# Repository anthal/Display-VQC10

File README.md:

# VQC10
DDR (WF) Punkt-Matrix-LED-Display VQC10 (Leiterplatte und Code)

Version 1

Version 2

## Leiterplatte Version 2
### Platine
* Farbe der Platine V.1 auf den Bildern: rot
* Farbe der Platine V.2 auf den Bildern: schwarz
* KiCAD 9 Projekt
* Die Platinen sind nebeneinander anreihbar und es können bis zu 4 Stück kaskadiert werden.
* Ab der 2. Platine geht es mit Flachbandkabel zur nächsten Platine. 
* Jede Platine wird über eine eigene Leitung (SD4-SD7) aktiviert. Die Auswahl erfolgt über die 4 Jumper.

### Halbleiterbauelemente
* 4 x VQC 10 (4-Digit-Punkt-Matrix-LED-Displays) 
* 3 x 74LS138 (1-aus-8 Dekoder für Zeilen und 1-aus-16 Dekoder für Digits)
* 1 x 74LS123 (Schutzschaltung)
* 7 x BD140 (Zeilentreiber)

### Anschlüsse Leiterplatte Version 1
**An 20 pol. Steckerleiste:**
* ZD0 - ZD2 (3): Zeilendecoder (U1, 74HCT138)
* SD0 - SD3 (4): Stellendecoder (U2, U3, 2x 74HCT138)
* SD4 - SD7 (4): Selektierung der Stellendecoder über Jumper (Low-Aktiv)
* D1-D5 (5): Daten (Zeilen)

**Belegung der Anschlüsse:**
| Pin | Belegung | Raspberry Pi Pico | LC80ex | Pin LC80-Userport |
|-----|----------|-------------------|--------|-------------------|
| 1   | +5 V     | +5 V              | +5 V   | 26                |
| 2   | +5 V     | +5 V              | +5 V   | 25                |
| 3   | SD0      | GP20              | PB0    | 16                |
| 4   | ZD0      | GP15              | PA0    | 21                |
| 5   | SD1      | GP19              | PB1    | 18                |
| 6   | ZD1      | GP14              | PA1    | 19                |
| 7   | SD2      | GP18              | PB2    | 20                |
| 8   | ZD2      | GP12              | PA2    | 17                |
| 9   | SD3      | GP17              | PB3    | 22                |
| 10  | D1       | GP28              | PA3    | 7                 |
| 11  | SD4      | GP16              | (Masse)| -                 |
| 12  | D2       | GP27              | PA4    | 9                 |
| 13  | SD5      | GP10              | (Masse)| -                 |
| 14  | D3       | GP26              | PA5    | 11                |
| 15  | SD6      | GP9               | (Masse)| -                 |
| 16  | D4       | GP22              | PA6    | 13                |
| 17  | SD7      | GP8               | (Masse)| -                 |
| 18  | D5       | GP21              | PA7    | 15                |
| 19  | Masse    | Masse             | Masse  | 1                 |
| 20  | Masse    | Masse             | Masse  | 2                 |

### Selektion der 4 Leiterplatten
SD4-7 müssen zur Selektierung Low und der jeweilige Jumper geschlossen sein:
| Leiterplatte | Jumper | Pin (J1/J2) | Belegung | Port-Pin (Raspberry Pi Pico) |
|---|-----|----|-----|------|
| 1 | JP1 | 11 | SD4 | GP16 |
| 2 | JP2 | 13 | SD5 | GP10 |
| 3 | JP3 | 15 | SD6 | GP9 |
| 4 | JP4 | 17 | SD7 | GP8 |

**Leiterplatte 1:** 
* Jumper JP1 geschlossen
* Jumper JP2 geöffnet
* Jumper JP3 geöffnet
* Jumper JP4 geöffnet

**Leiterplatte 2:**
* Jumper JP1 geöffnet
* Jumper JP2 geschlossen
* Jumper JP3 geöffnet
* Jumper JP4 geöffnet

**Leiterplatte 3:**
* Jumper JP1 geöffnet
* Jumper JP2 geöffnet
* Jumper JP3 geschlossen
* Jumper JP4 geöffnet

**Leiterplatte 4:**
* Jumper JP1 geöffnet
* Jumper JP2 geöffnet
* Jumper JP3 geöffnet
* Jumper JP4 geschlossen

## Literatur
* Datenblatt
* Schaltungen aus der rfe

## Simulation
* Simulation von 1x VQC10 mit Z80 unter SimulIDE
* https://simulide.com/

## Software
### Arduino Code
* Für den Raspberry Pi Pico
* auf Basis von https://github.com/versioduo/VQC10
* Vor Compilierung Example Datei und Files aus scr Verzeichnis in ein gemeinsames Verzeichnis verschieben

### Micropython Code
* Für den Raspberry Pi Pico

### Z80-Assembler
#### aZ80/RC2016-Computer

4x VQC10 am aZ80 Computer

Benutzte Entwicklungssoftware:
* "Small Computer-Monitor"
* https://smallcomputercentral.com/small-computer-monitor/

#### LC80ex

Test mit dem Nachbau des DDR-Platinen Computers LC80 

#### Z1013
ToDo

## Gehäuse

Grundplatte für IKEA Bilderrahmmen "VÄSTANHED 20x25 cm" mit Leiterplatten der Version 1
* STL Datei für 3D-Druck: "Gehäuse/2xVQC10_Grundplatte1.stl"

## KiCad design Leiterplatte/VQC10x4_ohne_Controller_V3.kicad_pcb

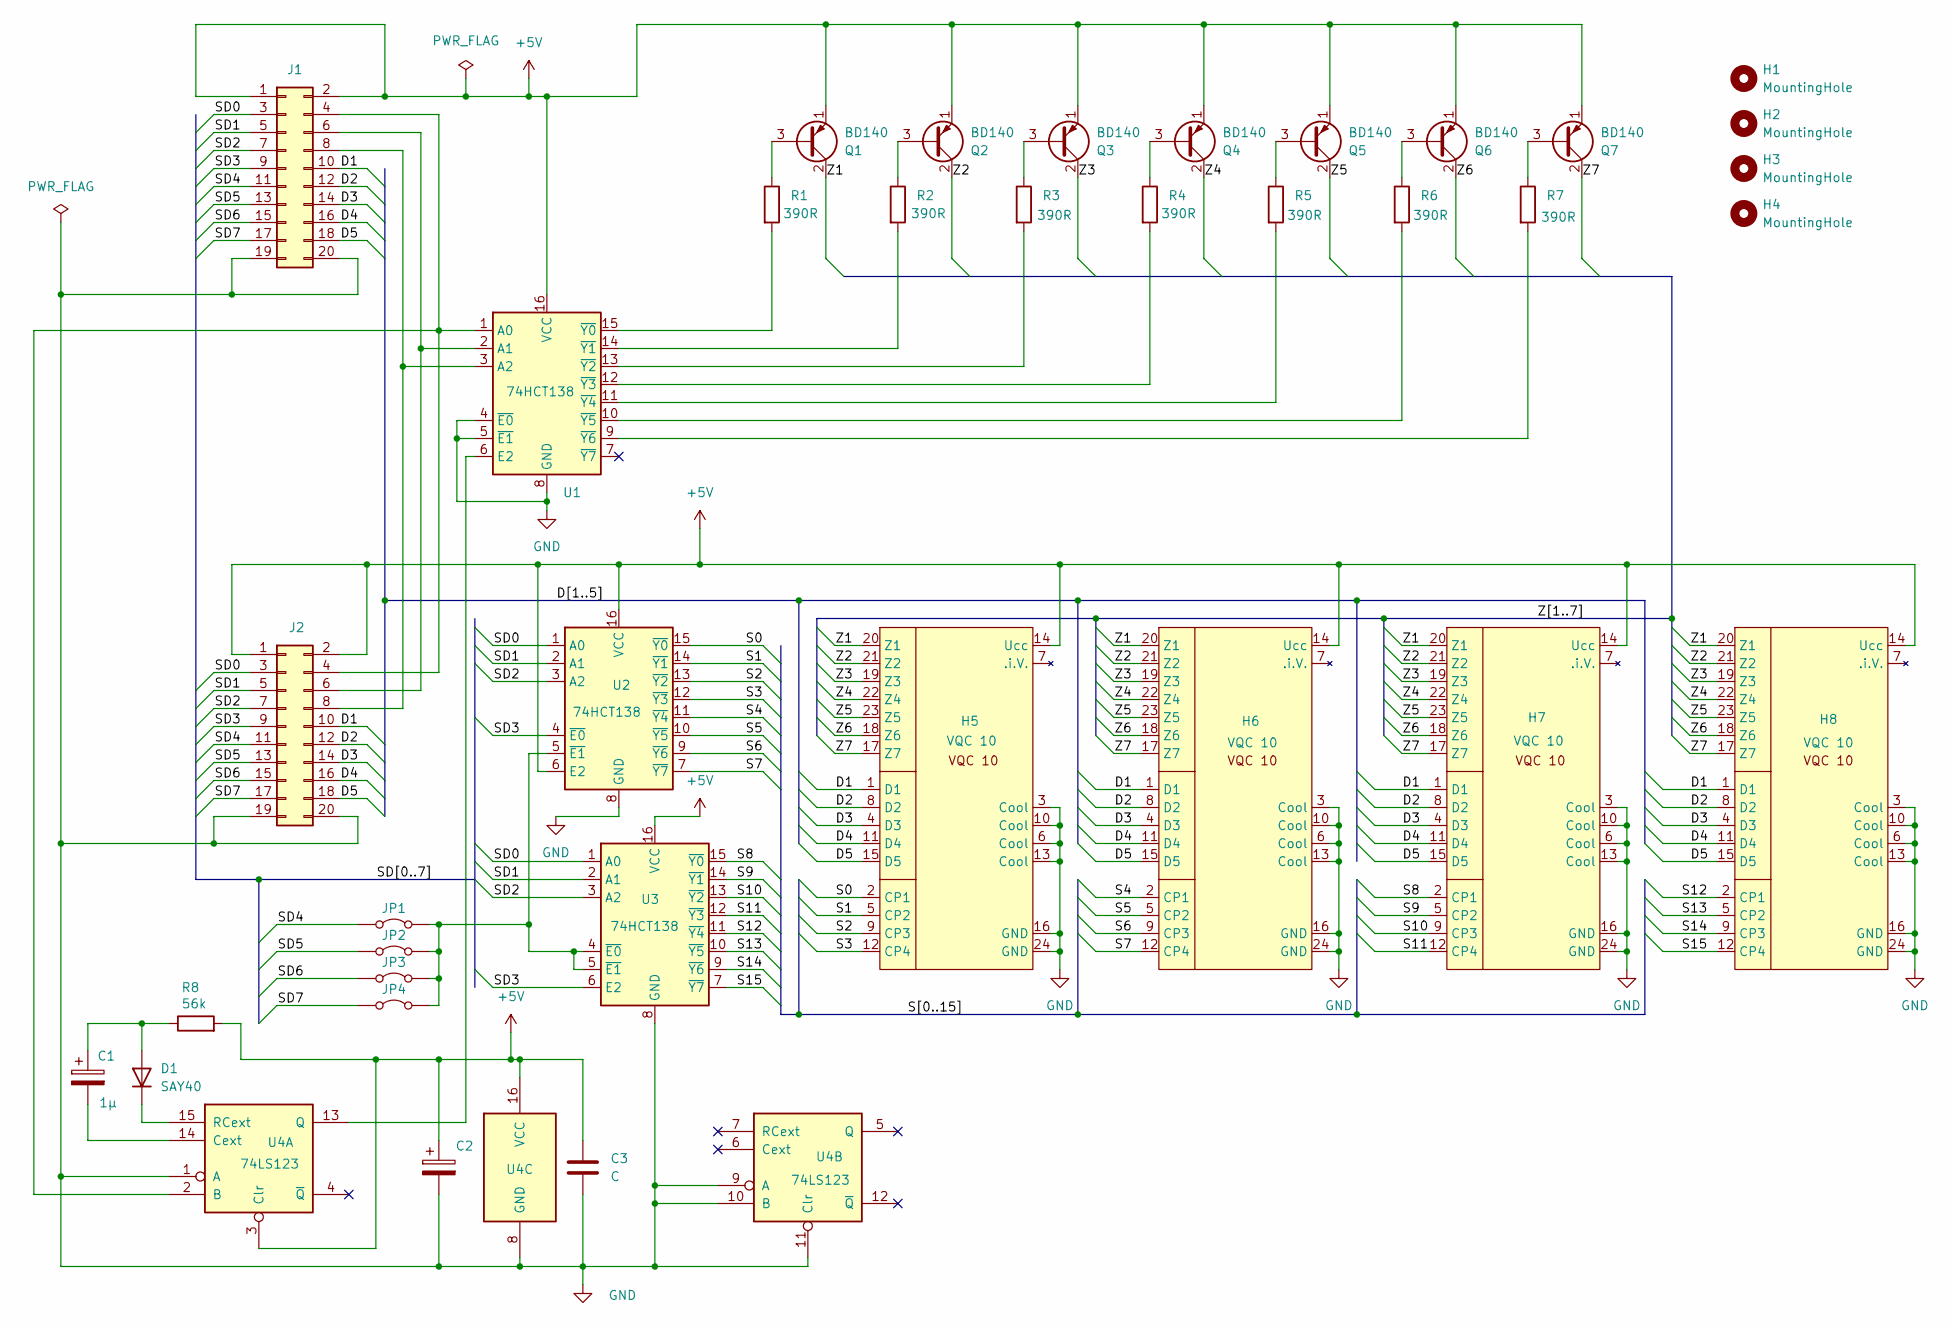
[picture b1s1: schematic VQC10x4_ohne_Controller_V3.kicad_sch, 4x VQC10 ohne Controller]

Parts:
C1: 1µ; CP_Radial_D5.0mm_P2.50mm
C2: C_Polarized; CP_Radial_D6.3mm_P2.50mm
C3: C; C_Disc_D5.0mm_W2.5mm_P2.50mm
D1: SAY40; D_A-405_P7.62mm_Horizontal
H1, H2, H3, H4: MountingHole; MountingHole_3.2mm_M3
H5, H6, H7, H8: VQC 10; VQC10
J1, J2: Conn_02x10_Odd_Even; IDC-Header_2x10_P2.54mm_Horizontal
JP1, JP2, JP3, JP4: Jumper_2_Bridged; TestPoint_2Pads_Pitch2.54mm_Drill0.8mm
Q1, Q2, Q3, Q4, Q5, Q6, Q7: BD140; TO-126-3_Vertical
R1, R2, R3, R4, R5, R6, R7: 390R; R_Axial_DIN0204_L3.6mm_D1.6mm_P5.08mm_Horizontal
R8: 56k; R_Axial_DIN0207_L6.3mm_D2.5mm_P7.62mm_Horizontal
U1, U2, U3: 74HCT138; DIP-16_W7.62mm_LongPads
U4: 74LS123; DIP-16_W7.62mm_LongPads

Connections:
+5V: C2.1, C3.1, H5.14 (Ucc), H6.14 (Ucc), H7.14 (Ucc), H8.14 (Ucc), J1.1, J1.2, J2.1, J2.2, Q1.1 (E), Q2.1 (E), Q3.1 (E), Q4.1 (E), Q5.1 (E), Q6.1 (E), Q7.1 (E), R8.2, U1.16 (VCC), U2.6 (E2), U2.16 (VCC), U3.16 (VCC), U4.3 (Clr), U4.16 (VCC)
/D1: H5.1 (D1), H6.1 (D1), H7.1 (D1), H8.1 (D1), J1.10, J2.10
/D2: H5.8 (D2), H6.8 (D2), H7.8 (D2), H8.8 (D2), J1.12, J2.12
/D3: H5.4 (D3), H6.4 (D3), H7.4 (D3), H8.4 (D3), J1.14, J2.14
/D4: H5.11 (D4), H6.11 (D4), H7.11 (D4), H8.11 (D4), J1.16, J2.16
/D5: H5.15 (D5), H6.15 (D5), H7.15 (D5), H8.15 (D5), J1.18, J2.18
/S0: H5.2 (CP1), U2.15 (~Y0)
/S1: H5.5 (CP2), U2.14 (~Y1)
/S2: H5.9 (CP3), U2.13 (~Y2)
/S3: H5.12 (CP4), U2.12 (~Y3)
/S4: H6.2 (CP1), U2.11 (~Y4)
/S5: H6.5 (CP2), U2.10 (~Y5)
/S6: H6.9 (CP3), U2.9 (~Y6)
/S7: H6.12 (CP4), U2.7 (~Y7)
/S8: H7.2 (CP1), U3.15 (~Y0)
/S9: H7.5 (CP2), U3.14 (~Y1)
/S10: H7.9 (CP3), U3.13 (~Y2)
/S11: H7.12 (CP4), U3.12 (~Y3)
/S12: H8.2 (CP1), U3.11 (~Y4)
/S13: H8.5 (CP2), U3.10 (~Y5)
/S14: H8.9 (CP3), U3.9 (~Y6)
/S15: H8.12 (CP4), U3.7 (~Y7)
/SD0: J1.3, J2.3, U2.1 (A0), U3.1 (A0)
/SD1: J1.5, J2.5, U2.2 (A1), U3.2 (A1)
/SD2: J1.7, J2.7, U2.3 (A2), U3.3 (A2)
/SD3: J1.9, J2.9, U2.4 (~E0), U3.6 (E2)
/SD4: J1.11, J2.11, JP1.1 (A)
/SD5: J1.13, J2.13, JP2.1 (A)
/SD6: J1.15, J2.15, JP3.1 (A)
/SD7: J1.17, J2.17, JP4.1 (A)
/Z1: H5.20 (Z1), H6.20 (Z1), H7.20 (Z1), H8.20 (Z1), Q1.2 (C)
/Z2: H5.21 (Z2), H6.21 (Z2), H7.21 (Z2), H8.21 (Z2), Q2.2 (C)
/Z3: H5.19 (Z3), H6.19 (Z3), H7.19 (Z3), H8.19 (Z3), Q3.2 (C)
/Z4: H5.22 (Z4), H6.22 (Z4), H7.22 (Z4), H8.22 (Z4), Q4.2 (C)
/Z5: H5.23 (Z5), H6.23 (Z5), H7.23 (Z5), H8.23 (Z5), Q5.2 (C)
/Z6: H5.18 (Z6), H6.18 (Z6), H7.18 (Z6), H8.18 (Z6), Q6.2 (C)
/Z7: H5.17 (Z7), H6.17 (Z7), H7.17 (Z7), H8.17 (Z7), Q7.2 (C)
GND: C2.2, C3.2, H5.3 (Cool), H5.6 (Cool), H5.10 (Cool), H5.13 (Cool), H5.16 (GND), H5.24 (GND), H6.3 (Cool), H6.6 (Cool), H6.10 (Cool), H6.13 (Cool), H6.16 (GND), H6.24 (GND), H7.3 (Cool), H7.6 (Cool), H7.10 (Cool), H7.13 (Cool), H7.16 (GND), H7.24 (GND), H8.3 (Cool), H8.6 (Cool), H8.10 (Cool), H8.13 (Cool), H8.16 (GND), H8.24 (GND), J1.19, J1.20, J2.19, J2.20, U1.4 (~E0), U1.5 (~E1), U1.8 (GND), U2.8 (GND), U3.8 (GND), U4.1 (A), U4.8 (GND), U4.9 (A), U4.10 (B), U4.11 (Clr)
unnamed: C1.1, D1.2 (A), R8.1
unnamed: D1.1 (K), U4.15 (RCext)
unnamed: J1.4, J2.4, U1.1 (A0), U4.2 (B)
unnamed: J1.6, J2.6, U1.2 (A1)
unnamed: J1.8, J2.8, U1.3 (A2)
unnamed: JP1.2 (B), JP2.2 (B), JP3.2 (B), JP4.2 (B), U2.5 (~E1), U3.4 (~E0), U3.5 (~E1)
unnamed: Q1.3 (B), R1.1
unnamed: Q2.3 (B), R2.1
unnamed: Q3.3 (B), R3.1
unnamed: Q4.3 (B), R4.1
unnamed: Q5.3 (B), R5.1
unnamed: Q6.3 (B), R6.1
unnamed: Q7.3 (B), R7.1
unnamed: U1.6 (E2), U4.13 (Q)
unnamed: R1.2, U1.15 (~Y0)
unnamed: R2.2, U1.14 (~Y1)
unnamed: R3.2, U1.13 (~Y2)
unnamed: R4.2, U1.12 (~Y3)
unnamed: R5.2, U1.11 (~Y4)
unnamed: R6.2, U1.10 (~Y5)
unnamed: R7.2, U1.9 (~Y6)
unnamed: C1.2, U4.14 (Cext)

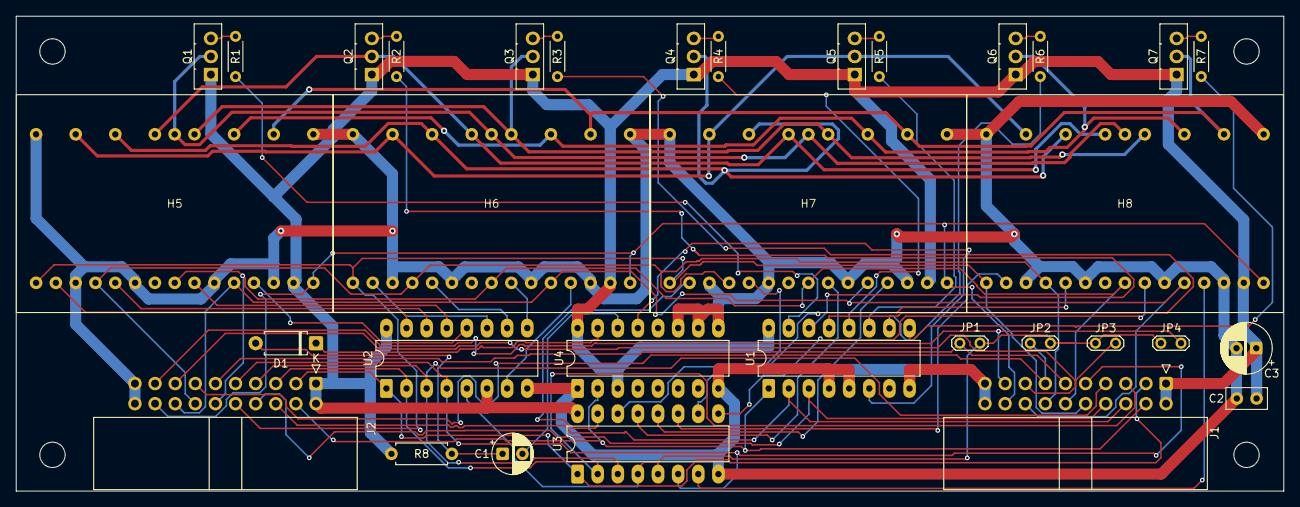
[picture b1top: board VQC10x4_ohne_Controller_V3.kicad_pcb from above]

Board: 2 copper layers, 160.0 x 59.9 mm, 37 parts (0 on the bottom side), 60 nets.

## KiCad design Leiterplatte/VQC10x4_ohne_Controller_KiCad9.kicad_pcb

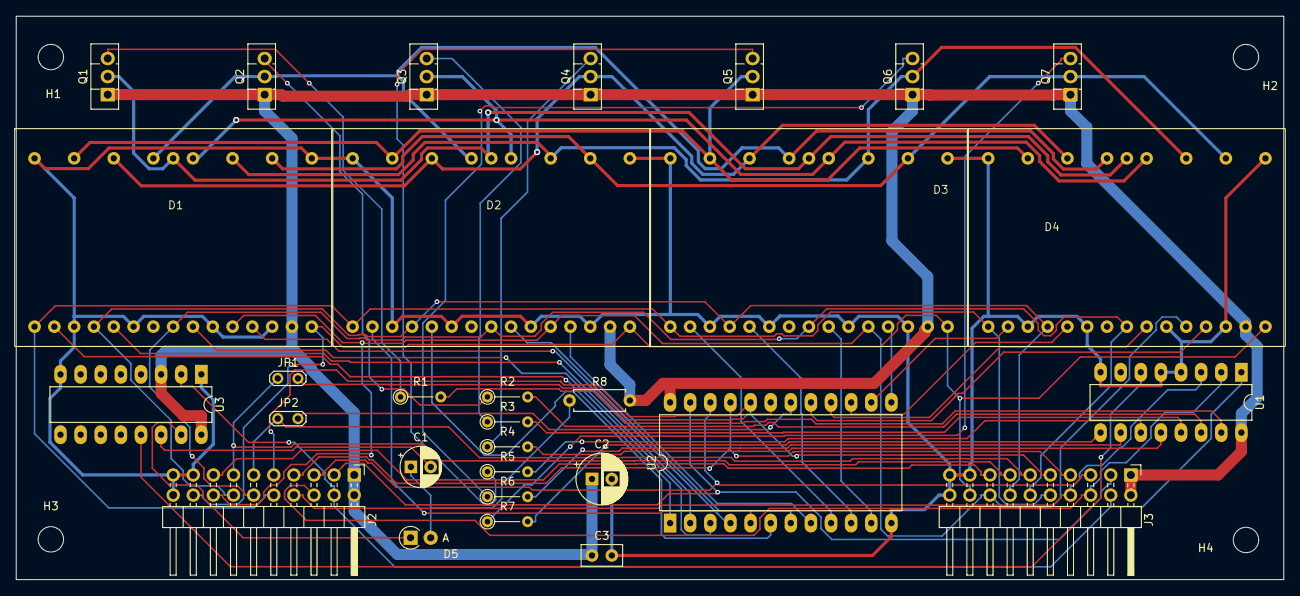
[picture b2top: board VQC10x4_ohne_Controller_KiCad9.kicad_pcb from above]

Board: 2 copper layers, 160.0 x 71.1 mm, 34 parts (0 on the bottom side), 60 nets.

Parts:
C1: 1µ; CP_Radial_D5.0mm_P2.50mm
C2: C_Polarized; CP_Radial_D6.3mm_P2.50mm
C3: C; C_Disc_D5.0mm_W2.5mm_P2.50mm
D1, D2, D3, D4: VQC 10; VQC10
D5: SAY40; D_A-405_P2.54mm_Vertical_AnodeUp
H1, H2, H3, H4: MountingHole; MountingHole_3.2mm_M3
J2, J3: Conn_02x10_Odd_Even; PinHeader_2x10_P2.54mm_Horizontal
JP1, JP2: Jumper_2_Bridged; TestPoint_2Pads_Pitch2.54mm_Drill0.8mm
Q1, Q2, Q3, Q4, Q5, Q6, Q7: BD140; TO-126-3_Vertical
R1, R2, R3, R4, R5, R6, R7: R; R_Axial_DIN0204_L3.6mm_D1.6mm_P5.08mm_Vertical
R8: 56k; R_Axial_DIN0207_L6.3mm_D2.5mm_P7.62mm_Horizontal
U1: 74HCT138; DIP-16_W7.62mm_LongPads
U2: 74LS154; DIP-24_W15.24mm_LongPads
U3: 74LS123; DIP-16_W7.62mm_LongPads

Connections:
+5V: C2.1, C3.1, D1.14 (Ucc), D2.14 (Ucc), D3.14 (Ucc), D4.14 (Ucc), J2.1, J2.2, J3.1, J3.2, Q1.1 (E), Q2.1 (E), Q3.1 (E), Q4.1 (E), Q5.1 (E), Q6.1 (E), Q7.1 (E), R8.2, U1.16 (VCC), U2.24 (VCC), U3.3 (Clr), U3.16 (VCC)
/D1: D1.1 (D1), D2.1 (D1), D3.1 (D1), D4.1 (D1), J2.10, J3.10
/D2: D1.8 (D2), D2.8 (D2), D3.8 (D2), D4.8 (D2), J2.12, J3.12
/D3: D1.4 (D3), D2.4 (D3), D3.4 (D3), D4.4 (D3), J2.14, J3.14
/D4: D1.11 (D4), D2.11 (D4), D3.11 (D4), D4.11 (D4), J2.16, J3.16
/D5: D1.15 (D5), D2.15 (D5), D3.15 (D5), D4.15 (D5), J2.18, J3.18
/S0: D1.2 (CP1), U2.1 (S0)
/S1: D1.5 (CP2), U2.2 (S1)
/S2: D1.9 (CP3), U2.3 (S2)
/S3: D1.12 (CP4), U2.4 (S3)
/S4: D2.2 (CP1), U2.5 (S4)
/S5: D2.5 (CP2), U2.6 (S5)
/S6: D2.9 (CP3), U2.7 (S6)
/S7: D2.12 (CP4), U2.8 (S7)
/S8: D3.2 (CP1), U2.9 (S8)
/S9: D3.5 (CP2), U2.10 (S9)
/S10: D3.9 (CP3), U2.11 (S10)
/S11: D3.12 (CP4), U2.13 (S11)
/S12: D4.2 (CP1), U2.14 (S12)
/S13: D4.5 (CP2), U2.15 (S13)
/S14: D4.9 (CP3), U2.16 (S14)
/S15: D4.12 (CP4), U2.17 (S15)
/SD0: J2.3, J3.3, U2.23 (A0)
/SD1: J2.5, J3.5, U2.22 (A1)
/SD2: J2.7, J3.7, U2.21 (A2)
/SD3: J2.9, J3.9, U2.20 (A3)
/SD4: J2.11, J3.11, JP2.1 (A)
/SD5: J2.13, J3.13, JP1.1 (A)
/SD6: J2.15, J3.15
/Z1: D1.20 (Z1), D2.20 (Z1), D3.20 (Z1), D4.20 (Z1), Q1.2 (C)
/Z2: D1.21 (Z2), D2.21 (Z2), D3.21 (Z2), D4.21 (Z2), Q2.2 (C)
/Z3: D1.19 (Z3), D2.19 (Z3), D3.19 (Z3), D4.19 (Z3), Q3.2 (C)
/Z4: D1.22 (Z4), D2.22 (Z4), D3.22 (Z4), D4.22 (Z4), Q4.2 (C)
/Z5: D1.23 (Z5), D2.23 (Z5), D3.23 (Z5), D4.23 (Z5), Q5.2 (C)
/Z6: D1.18 (Z6), D2.18 (Z6), D3.18 (Z6), D4.18 (Z6), Q6.2 (C)
/Z7: D1.17 (Z7), D2.17 (Z7), D3.17 (Z7), D4.17 (Z7), Q7.2 (C)
GND: C2.2, C3.2, D1.3 (Cool), D1.6 (Cool), D1.10 (Cool), D1.13 (Cool), D1.16 (GND), D1.24 (GND), D2.3 (Cool), D2.6 (Cool), D2.10 (Cool), D2.13 (Cool), D2.16 (GND), D2.24 (GND), D3.3 (Cool), D3.6 (Cool), D3.10 (Cool), D3.13 (Cool), D3.16 (GND), D3.24 (GND), D4.3 (Cool), D4.6 (Cool), D4.10 (Cool), D4.13 (Cool), D4.16 (GND), D4.24 (GND), J2.17, J2.19, J2.20, J3.17, J3.19, J3.20, U1.4 (~E0), U1.5 (~E1), U1.8 (GND), U2.12 (GND), U3.1 (A), U3.8 (GND)
unnamed: C1.1, D5.2 (A), R8.1
unnamed: D5.1 (K), U3.15 (RCext)
unnamed: J2.4, J3.4, U1.1 (A0), U3.2 (B)
unnamed: J2.6, J3.6, U1.2 (A1)
unnamed: J2.8, J3.8, U1.3 (A2)
unnamed: JP1.2 (B), U2.19 (E1)
unnamed: JP2.2 (B), U2.18 (E0)
unnamed: Q1.3 (B), R1.1
unnamed: Q2.3 (B), R2.1
unnamed: Q3.3 (B), R3.1
unnamed: Q4.3 (B), R4.1
unnamed: Q5.3 (B), R5.1
unnamed: Q6.3 (B), R6.1
unnamed: Q7.3 (B), R7.1
unnamed: U1.6 (E2), U3.13 (Q)
unnamed: R1.2, U1.15 (~Y0)
unnamed: R2.2, U1.14 (~Y1)
unnamed: R3.2, U1.13 (~Y2)
unnamed: R4.2, U1.12 (~Y3)
unnamed: R5.2, U1.11 (~Y4)
unnamed: R6.2, U1.10 (~Y5)
unnamed: R7.2, U1.9 (~Y6)
unnamed: C1.2, U3.14 (Cext)

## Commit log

2026-01-17 Erste Commit
2026-01-18 Update Leiterplatten, Bild und Literatur
2026-01-18 Update Schaltplan + PDF
2026-01-18 Entfernung überflüssiger Python Pakete
2026-01-18 CHG: Bilderverzeichnis geändert und in readme eingefügt
2026-01-18 CHG: Neuordnung der Arduino Files
2026-01-18 CHG: Update readme Datei
2026-01-21 ADD: Initialer Text vor erstem Empfang
2026-01-22 CHG: Optimierung der Beispiele
2026-01-22 CHG: WLAN Passwort und SSID in extra Datei auslagern
2026-01-23 ADD: mehr Infos auf VQC10 und Kapselung Displayausgabe
2026-02-14 ADD: Beispiel für 32 Stelliges Display (8x VQC10)
2026-02-14 ADD: Bild vom 8x VQC10 Display
2026-02-14 ADD: Bild mit 8x VQC10 in readme
2026-02-28 ADD: Simulation mit SimulIDE
2026-02-28 ADD: Bild von Simulation
2026-02-28 ADD: Neues Bild - "4x VQC10 am aZ80 Computer"
2026-02-28 CHG: Änderung Bildname
2026-02-28 ADD: Z80-Assembler Code
2026-02-28 CHG: Formatierung readme.md
2026-03-04 ADD: Assembler Code für den LC80ex
2026-03-05 CHG: Verbesserung der Deaktivierung des Stellendekoders
2026-03-06 CHG: Readme überarbeitet
2026-03-06 CHG: Formatierung der Readme repariert
2026-03-06 CHG: readme ACHTUNG in Fett
2026-03-06 ADD: Bild VQC10 am LC80ex
2026-03-06 CHG: anderer Filenamen für LC80 Bild
2026-03-06 CHG: Erweiterung Readme
2026-03-07 ADD: 3D-Grundplatte + Bild
2026-03-07 CHG: Abschnitt Gehäuse in Readme
2026-04-06 UPD: Neue Leiterplattenversion
2026-04-06 CHG: Anpassung der Simulation an Leiterplatte V2
